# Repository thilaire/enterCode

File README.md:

# enterCode

This is a small toy for my children:
- they want a small keyboard to "simulate" a code to enter their room
- a green LED will light on when the code is correct (red if not)
- they will also be able to use a RFID key

It is powered by three AA battery, and should not consume too much (sleep mode)

# Principle

# Bill of Material
- an AVR micro-controller (ATtiny 2313)
- a small 4x4 matrix keyboard (
- 3 AA 1.5v battery (and their holder)
- two LEDs (green and red)
- a plastic box
- a RC522 RFID reader and some RFID key
- four 7-segment displays, with TM1637 driver

# Some links
- [doc for the RC522 board](https://www.sunrom.com/p/mifare-rfid-readerwriter-1356mhz-rc522)

# To Do (not yet done, but will be done... one day in the future)
- go to sleep mode after 20 seconds (when not used)
- RFID part

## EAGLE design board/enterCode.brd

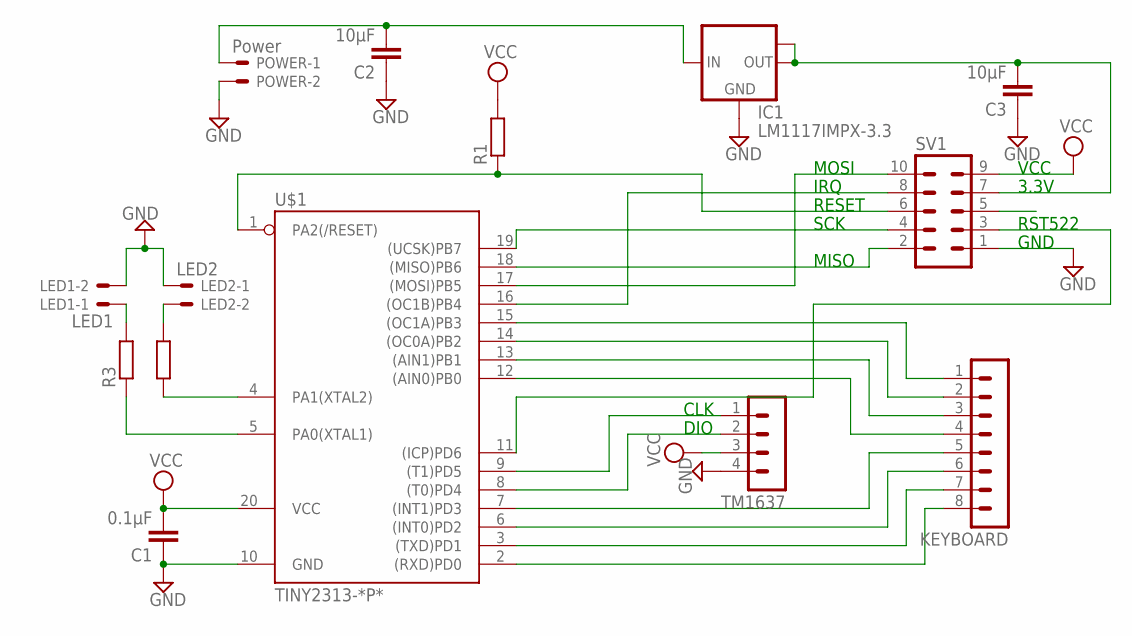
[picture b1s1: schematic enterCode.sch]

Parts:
C1: 0.1µF; C2.5-4
C2, C3: 10µF; C2.5-4
IC1: LM1117IMPX-3.3; SOT223
KEYBOARD: MA08-1
LED1: LED1; 22-23-2021
LED2: LED2; 22-23-2021
POWER: Power; 22-23-2021
R1: 10k; 0207/10
R2, R3: 470; 0207/10
SV1: MA05-2
TM1637: MA04-1
U$1: TINY2313-*P*; DIL20

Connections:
3.3V: C3.2, IC1.2 (OUT), IC1.TAB (OUT1), SV1.7
+5V: C2.2, IC1.3 (IN), POWER.1
GND: C1.1, C2.1, C3.1, IC1.1 (GND), LED1.2, LED2.1, POWER.2, SV1.1, TM1637.4, U$1.10 (GND)
MISO: SV1.2, U$1.18 ((MISO)PB6)
MOSI: SV1.10, U$1.17 ((MOSI)PB5)
unnamed: LED1.1, R3.2
unnamed: LED2.2, R2.2
PA0: R3.1, U$1.5 (PA0(XTAL1))
PA1: R2.1, U$1.4 (PA1(XTAL2))
PB0: KEYBOARD.4, U$1.12 ((AIN0)PB0)
PB1: KEYBOARD.3, U$1.13 ((AIN1)PB1)
PB2: KEYBOARD.2, U$1.14 ((OC0A)PB2)
PB3: KEYBOARD.1, U$1.15 ((OC1A)PB3)
PB4: SV1.8, U$1.16 ((OC1B)PB4)
PD0: KEYBOARD.8, U$1.2 ((RXD)PD0)
PD1: KEYBOARD.7, U$1.3 ((TXD)PD1)
PD2: KEYBOARD.6, U$1.6 ((INT0)PD2)
PD3: KEYBOARD.5, U$1.7 ((INT1)PD3)
PD4: TM1637.2, U$1.8 ((T0)PD4)
PD5: TM1637.1, U$1.9 ((T1)PD5)
PD6: SV1.3, U$1.11 ((ICP)PD6)
RESET: R1.1, SV1.6, U$1.1 (PA2(/RESET))
SCK: SV1.4, U$1.19 ((UCSK)PB7)
VCC: C1.2, R1.2, SV1.9, TM1637.3, U$1.20 (VCC)

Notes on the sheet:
CLK
DIO
RESET
SCK
MISO
IRQ
RST522
3.3V
GND
MOSI
VCC

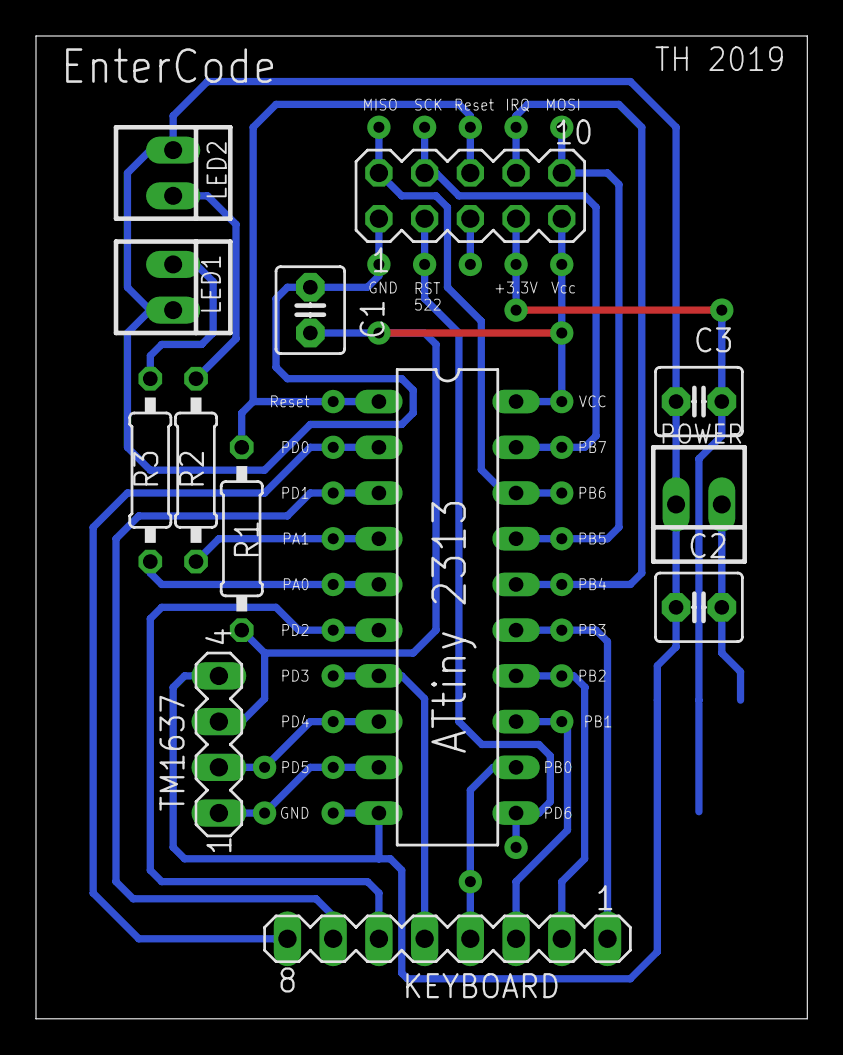
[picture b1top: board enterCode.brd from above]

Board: 2 copper layers, 42.8 x 54.6 mm, 14 parts (1 on the bottom side), 24 nets.

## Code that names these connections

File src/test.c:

#include <util/delay.h>
#include <avr/io.h>

#include "TM1637.h"

/* input/output
 * PA0: (out) LED1                  PB0: (in) Keyboard 0
 * PA1: (out) LED2                  PB1: (in) Keyboard 1
 * PD0: (out) Keyboard 0            PB2: (in) Keyboard 2
 * PD1: (out) Keyboard 1            PB3: (in) Keyboard 3
 * PD2: (out) Keyboard 2            PB4: (in) RS522 IRQ
 * PD3: (out) Keyboard 3            PB5: (out) SPI MOSI
 * PD4: (out) TM1637 DIO            PB6: (out) SPI MISO
 * PD5: (out) TM1637 CLK            PB7: (out) SPI SCK
 * PD6: (???) RS522
*/


/* debug */
const uint8_t NUMBER_FONT[] = {
		0b00111111, // 0
		0b00000110, // 1
		0b01011011, // 2
		0b01001111, // 3
		0b01100110, // 4
		0b01101101, // 5
		0b01111101, // 6
		0b00000111, // 7
		0b01111111, // 8
		0b01101111, // 9
		0b01110111, // A
		0b01111100, // B
		0b00111001, // C
		0b01011110, // D
		0b01111001, // E
		0b01110001  // F
};



int main()
{
    /* input/output config */
	DDRA = 0b00000011;       /* PA0 and PA1 are output */
    DDRB = 0b11100000;       /* PB0 to PB4 are output, PB5 to PB7 are output */
    DDRD = 0b11111111;       /* PD0 to PD7 are output */


    /* test */
    TM1637_setup(0);
    TM1637_write4(NUMBER_FONT[7],NUMBER_FONT[3],NUMBER_FONT[6],NUMBER_FONT[1]);

	//TM1637_write(NUMBER_FONT[7],0);
	//TM1637_write(NUMBER_FONT[1],1);
    //TM1637_write(NUMBER_FONT[3],2);
	//TM1637_write(NUMBER_FONT[6],3);


	while(1){
		PORTA = 0b00000001;
		_delay_ms(500);
		PORTA = 0b00000010;
		_delay_ms(500);	
	}

}

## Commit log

2018-02-17 add link to RC522 resources
2019-02-06 add the board
2019-02-06 add the MFRC522 datasheet (RFID reader)
2019-02-06 add .gitignore file for C (and co)
2019-02-06 add minor details
2019-02-06 remove all files from JetBrain IDE (CLion)
2019-02-18 add some datasheet
2019-02-18 add support for the TM1637 display
2019-02-19 add pdf for the schematic
2019-02-19 add support for the keyboard
2019-02-19 simplified code (no rotation buffer anymore, but size-limited buffer instead)
2019-02-19 reset code when validated with `#`
2019-02-19 read/write the codes from the EEPROM
2019-02-19 add the Makefile (`make fuses` to program the fuses the 1st time, `make program` to program the ATtiny, and `make eeprom` to import the 1st EEPROM with 123456 as master code)
2019-02-20 regroup the EEPROM function into one file
2019-02-20 add nice header
2019-02-20 correct import
2019-02-20 compile the eeprom.c file
2019-02-20 code cleanup
2019-02-20 regroup the code functions into the codes.c/codes.h files
2019-02-20 [untested] add the change code functionality
2019-02-20 update delays
2019-02-20 [untested] the same, but using the EEPROM functions from the avr libc (avr/eeprom.h) -> the eeprom.c and eeprom.h files are not necessary
2019-02-20 can only change codes for number < NB_CODES
2019-02-20 display the number of the code that is changed in MASTER mode
2019-02-20 the eeprom files are no more required (we use the avr/eeprom functions)
2019-02-22 Correct a MAJOR error in the design: the TAB of the regulator LM1117-3.3V is not corrected to GND (as it was) *but* to 3.3V signal !!
2019-03-04 turn on the two LEDs during initialization
2019-03-04 adjust the delays so that it works under 3.3V !!
2019-04-05 updated pdf (after the MAJOR correction)
2019-04-05 resized photos
2019-04-05 add photo
